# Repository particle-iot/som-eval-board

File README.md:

# M.2 SoM Evaluation Board

*Hardware repository for the M.2 SoM evaluation board*

The description of the board and its features can be found in the documentation:

[https://docs.particle.io/datasheets/cellular/b-series-eval-board/](https://docs.particle.io/datasheets/cellular/b-series-eval-board/)

In this repository you can find the following directories:

- eagle: The [Eagle CAD](https://www.autodesk.com/products/eagle/overview) design files for this board. Note that it is a 4-layer board so you won't be able to edit it with the free version.
- gerbers: The Gerber files used to manufacture the board.
- bom: The bill of materials (Excel spreadsheet).

Other useful resources include:

- [Creating your first SoM board tutorial](https://docs.particle.io/tutorials/hardware-projects/som-first-board/).
- [AN001 Basic SoM Design](https://github.com/particle-iot/app-notes/tree/master/AN001-Basic-SoM-Design) is a simple SoM base board. Like a Boron it can be powered by LiPo battery, USB, or an external DC supply. It includes: RGB LED, bq24195 PMIC, MAX17043 Fuel Gauge, USB Connector, LiPo Connector (JST-PH), and M.2 SoM Connector. It is a 2-layer board.

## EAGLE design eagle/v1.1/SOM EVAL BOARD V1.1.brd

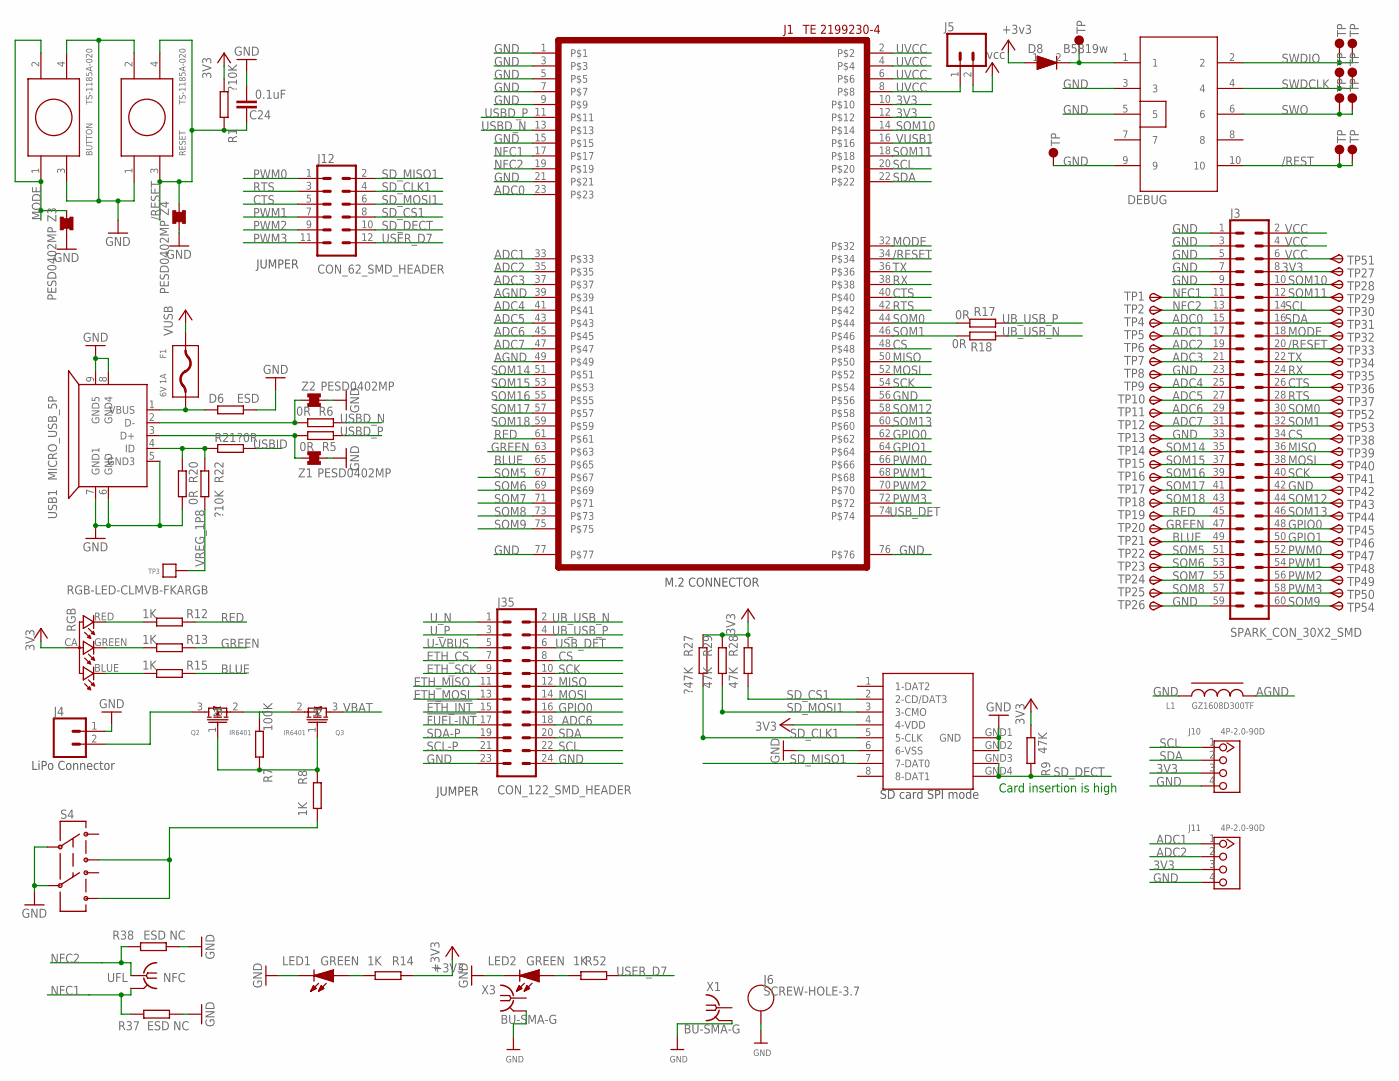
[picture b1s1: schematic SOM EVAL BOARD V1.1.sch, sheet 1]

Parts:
BUTTON: TS-1185A-020
C24: 0.1uF; C0402_B
D6: ESD; R-0402S
D8: B5819w; SOD-123
DEBUG: CON5X2; CON5X2_1.27
F1: 6V 1A; F0805
J1: TE 2199230-4; M.2EKEY
J3: SPARK_CON_30X2_SMD
J4: CONN_02-JST-2MM-SMT; JST-2-SMD
J5: CONN_02; 1X02
J6: SCREW-HOLE-3.7
J10, J11: 4P-2.0-90D; HW4-2.0-90D
J12: CON_62_SMD_HEADER; CON_6*2_SMD_HEADER
J35: CON_122_SMD_HEADER; CON_12*2_SMD_HEADER
L1: GZ1608D300TF; R-0603A
LED1, LED2: GREEN; LED0603
NFC: UFL; IPEX-20279-001E
P1, P2, P3, P4: SPARK_POGOPIN; SPARK_POGO-2.0
Q2, Q3: IR6401; SOT-23
R1, R22: ?10K; R-0402S
R5, R6, R17, R18, R20: 0R; R-0402S
R7: 100K; R0603
R8, R12, R13, R14, R15, R52: 1K; R-0402S
R9, R28, R29: 47K; R-0402S
R21: ?0R; R-0402S
R27: ?47K; R-0402S
R37, R38: ESD NC; R-0402S
RESET: TS-1185A-020
RGB: RGB-LED-CLMVB-FKARGB; PLCC4-2MM-RGB
S4: SWITCH-DPDT; SWITCH-2.5X3.2-6
TP1, TP2, TP4, TP5, TP6, TP7, TP8, TP9, TP10, TP11, TP12, TP13, TP14, TP15, TP16, TP17, TP18, TP19, TP20, TP21, TP22, TP23, TP24, TP25, TP26, TP27, TP28, TP29, TP30, TP31, TP32, TP33, TP34, TP35, TP36, TP37, TP38, TP39, TP40, TP41, TP42, TP43, TP44, TP45, TP46, TP47, TP48, TP49, TP50, TP51, TP52, TP53, TP54: TPSB1,27; B1,27
TP3: TPTP; TP
U$1, U$2, U$9, U$10, U$11, U$12: TP2; TP70_BOT
USB1: MICRO_USB_5P; MICRO_USB
X1, X3: BU-SMA-G
X4: 0046_15TW-882; SDCARD-15TW-8821
Z1, Z2, Z3, Z4: PESD0402MP; SMD-0402MP

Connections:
3V3: J1.10, J1.12, J3.8, J10.3, J11.3, R1.2, R9.2, R27.1, R28.1, R29.1, RGB.CA (1), TP27.TP, X4.4 (4-VDD); also elsewhere on the board
!ETH_INT: J35.15; also elsewhere on the board
!FUEL-INT: J35.17; also elsewhere on the board
+3V3: D8.1, R14.1; also elsewhere on the board
/RESET: C24.2, J1.34, J3.20, R1.1, RESET.3, RESET.4, TP33.TP, Z4.2
/REST: DEBUG.10, P4.P$2, U$12.P$1
ADC0: J1.23, J3.15, TP4.TP
ADC1: J1.33, J3.17, J11.1, TP5.TP
ADC2: J1.35, J3.19, J11.2, TP6.TP
ADC3: J1.37, J3.21, TP7.TP
ADC4: J1.41, J3.25, TP9.TP
ADC5: J1.43, J3.27, TP10.TP
ADC6: J1.45, J3.29, J35.18, TP11.TP
ADC7: J1.47, J3.31, TP12.TP; also elsewhere on the board
AGND: J1.39, J1.49, L1.2
BLUE: J1.65, J3.49, R15.1, TP21.TP
CS: J1.48, J3.34, J35.8, TP38.TP
CTS: J1.40, J3.26, J12.5, TP36.TP
D+: R5.2, USB1.3 (D+), Z1.2
D-: R6.2, USB1.2 (D-), Z2.2
ETH_CS: J35.7; also elsewhere on the board
ETH_MISO: J35.11; also elsewhere on the board
ETH_MOSI: J35.13; also elsewhere on the board
ETH_SCK: J35.9; also elsewhere on the board
GND: BUTTON.3, BUTTON.4, C24.1, D6.1, DEBUG.3, DEBUG.5, DEBUG.9, J1.1, J1.3, J1.5, J1.7, J1.9, J1.15, J1.21, J1.56, J1.76, J1.77, J3.1, J3.3, J3.5, J3.7, J3.9, J3.23, J3.33, J3.42, J3.59, J4.1 (2), J6.P$1, J10.4, J11.4, J35.23, J35.24, L1.1, LED1.2 (K), LED2.2 (K), R20.2, R37.2, R38.1, RESET.1, RESET.2, S4.2, S4.5, TP8.TP, TP13.TP, TP26.TP, TP42.TP, U$2.P$1, USB1.5 (GND3), USB1.6 (GND), USB1.7 (GND1), USB1.8 (GND4), USB1.9 (GND5), X1.2, X1.3 (2), X1.4 (2), X1.5 (2), X3.2, X3.3 (2), X3.4 (2), X3.5 (2), X4.6 (6-VSS), X4.GND1 (GND), X4.GND2 (GND1), Z1.1, Z2.1, Z3.1, Z4.1; also elsewhere on the board
GPIO0: J1.62, J3.48, J35.16, TP45.TP
GPIO1: J1.64, J3.50, TP46.TP
GREEN: J1.63, J3.47, R13.1, TP20.TP
MISO: J1.50, J3.36, J35.12, TP39.TP
MODE: BUTTON.1, BUTTON.2, J1.32, J3.18, TP32.TP, Z3.2
MOSI: J1.52, J3.38, J35.14, TP40.TP
unnamed: R20.1, R21.1, R22.1, USB1.4 (ID)
unnamed: R12.2, RGB.RED (4)
unnamed: R8.2, S4.3, S4.6
unnamed: D8.2, DEBUG.1, U$1.P$1
unnamed: J4.2 (1), Q2.3
unnamed: D6.2, F1.P$1 (1), USB1.1 (VBUS)
unnamed: LED1.1 (A), R14.2
unnamed: R15.2, RGB.BLUE (2)
unnamed: R13.2, RGB.GREEN (3)
unnamed: LED2.1 (A), R52.2
unnamed: Q2.2, Q3.2, R7.2
unnamed: Q2.1, Q3.1, R7.1, R8.1
NFC1: J1.17, J3.11, NFC.2@1 (GND), NFC.2@2 (GND), R37.1, TP1.TP
NFC2: J1.19, J3.13, NFC.1, R38.2, TP2.TP
PWM0: J1.66, J3.52, J12.1, TP47.TP
PWM1: J1.68, J3.54, J12.7, TP48.TP
PWM2: J1.70, J3.56, J12.9, TP49.TP
PWM3: J1.72, J3.58, J12.11, TP50.TP
RED: J1.61, J3.45, R12.1, TP19.TP
RTS: J1.42, J3.28, J12.3, TP37.TP
RX: J1.38, J3.24, TP35.TP
SCK: J1.54, J3.40, J35.10, TP41.TP
SCL: J1.20, J3.14, J10.1, J35.22, TP30.TP
SCL-P: J35.21; also elsewhere on the board
SDA: J1.22, J3.16, J10.2, J35.20, TP31.TP
SDA-P: J35.19; also elsewhere on the board
SD_CLK1: J12.4, R27.2, X4.5 (5-CLK)
SD_CS1: J12.8, R28.2, X4.2 (2-CD/DAT3)
SD_DECT: J12.10, R9.1, X4.GND3 (GND2), X4.GND4 (GND3)
SD_MISO1: J12.2, X4.7 (7-DAT0)
SD_MOSI1: J12.6, R29.2, X4.3 (3-CMO)
SOM0: J1.44, J3.30, R17.2, TP52.TP
SOM1: J1.46, J3.32, R18.2, TP53.TP
SOM5: J1.67, J3.51, TP22.TP
SOM6: J1.69, J3.53, TP23.TP
SOM7: J1.71, J3.55, TP24.TP
SOM8: J1.73, J3.57, TP25.TP
SOM9: J1.75, J3.60, TP54.TP
SOM10: J1.14, J3.10, TP28.TP
SOM11: J1.18, J3.12, TP29.TP
SOM12: J1.58, J3.44, TP43.TP
SOM13: J1.60, J3.46, TP44.TP
SOM14: J1.51, J3.35, TP14.TP
SOM15: J1.53, J3.37, TP15.TP
SOM16: J1.55, J3.39, TP16.TP
SOM17: J1.57, J3.41, TP17.TP
SOM18: J1.59, J3.43, TP18.TP
SWDCLK: DEBUG.4, P2.P$2, U$10.P$1
SWDIO: DEBUG.2, P1.P$2, U$9.P$1
SWO: DEBUG.6, P3.P$2, U$11.P$1
TX: J1.36, J3.22, TP34.TP
U-VBUS: J35.5; also elsewhere on the board
UB_USB_N: J35.2, R18.1
UB_USB_P: J35.4, R17.1
USBD_N: J1.13, R6.1; also elsewhere on the board
USBD_P: J1.11, R5.1; also elsewhere on the board
USBID: R21.2
USB_DET: J1.74, J35.6
USER_D7: J12.12, R52.1
UVCC: J1.2, J1.4, J1.6, J1.8, J5.1
U_N: J35.1; also elsewhere on the board
U_P: J35.3; also elsewhere on the board
VBAT: Q3.3; also elsewhere on the board
VCC: J3.2, J3.4, J3.6, J5.2, TP51.TP; also elsewhere on the board
VREG_1P8: R22.2, TP3.P$1
VUSB: F1.P$2 (2); also elsewhere on the board
VUSB1: J1.16; also elsewhere on the board

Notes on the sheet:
SD card SPI mode
LiPo Connector
JUMPER
Card insertion is high
M.2 CONNECTOR

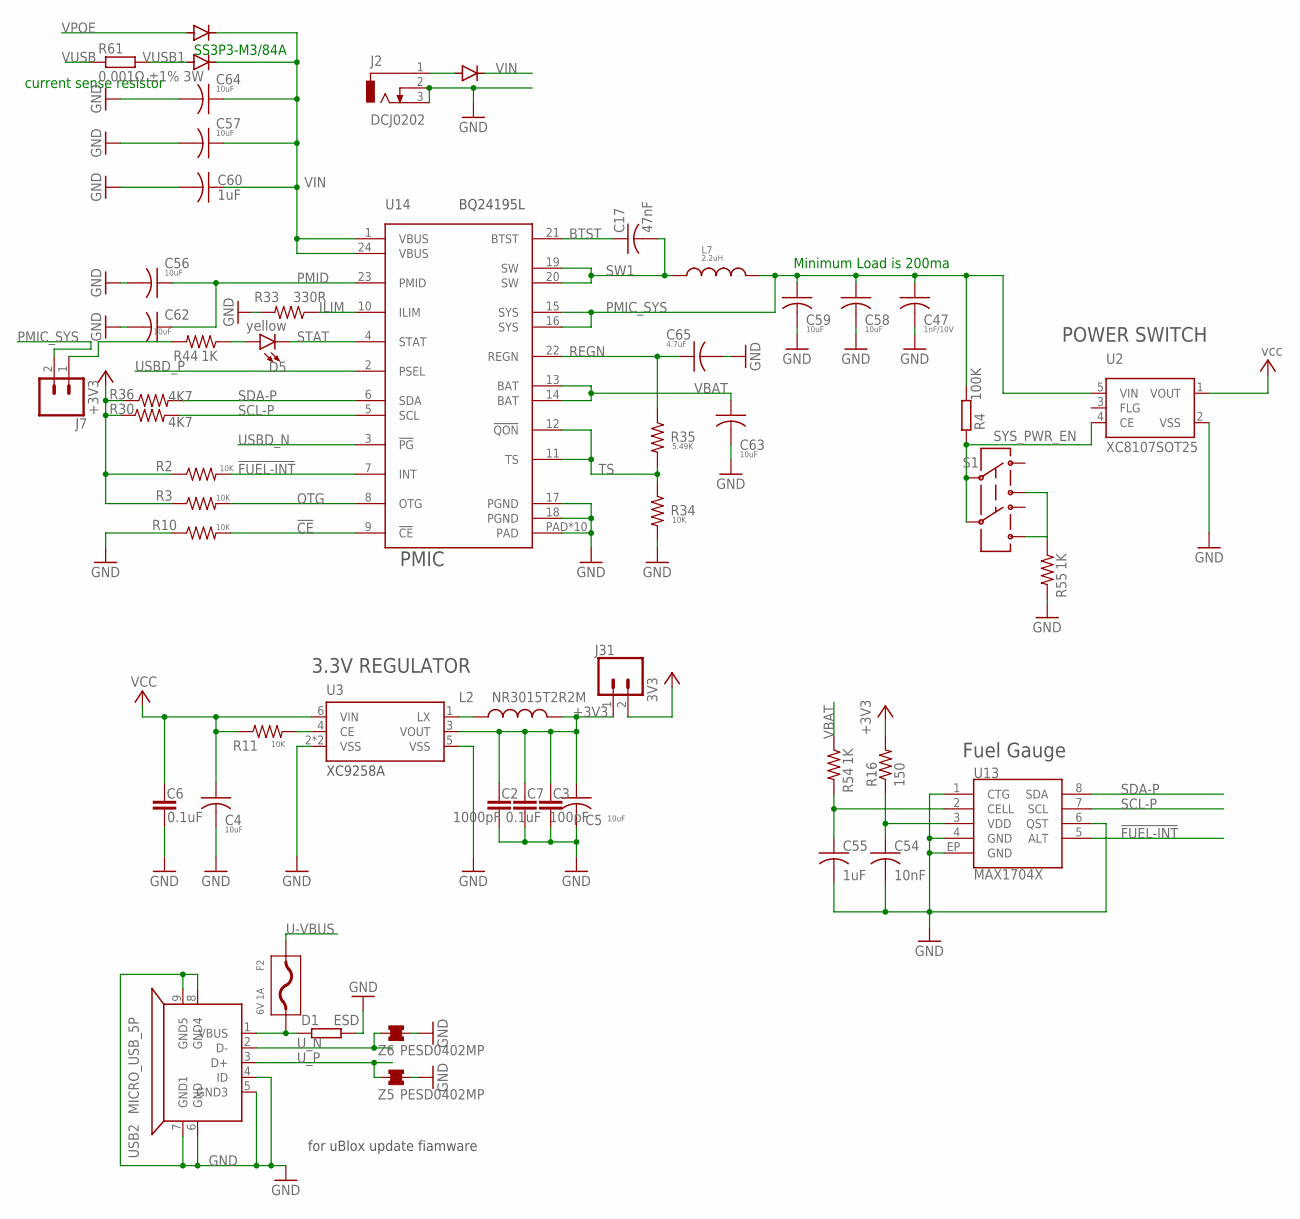
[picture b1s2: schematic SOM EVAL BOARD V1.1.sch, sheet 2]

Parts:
C2: 1000pF; C0402_B
C3: 100pF; C0402_B
C4, C5, C56, C57, C58, C59, C62, C63, C64: 10uF; C0603_B
C6, C7: 0.1uF; C0402_B
C17: 47nF; C0201_B
C47: 1nF/10V; C0402_B
C54: 10nF; C0402_B
C55, C60: 1uF; C0402_B
C65: 4.7uF; C0603_B
D1: ESD; R-0402S
D3, D4, D7: SS3P3-M3/84A; DIODE-DO-220AA_NT(SMP)
D5: yellow; LED-0603
F2: 6V 1A; F0805
J2: DCJ0202
J7, J31: CONN_02; 1X02
L2: NR3015T2R2M; INDUCTOR-VLS-E
L7: 2.2uH; INDUCTOR-4040
R2, R3, R10, R11, R34: 10K; R0402_B
R4: 100K; R0603
R16: 150; 0402-RES
R30, R36: 4K7; C0201_B
R33: 330R; R0402_B
R35: 5.49K; R0402_B
R44, R54, R55: 1K; R0402_B
R61: 0.001Ω ±1% 3W; R2512
S1: SWITCH-DPDT; SWITCH-2.5X3.2-6
U2: XC8107SOT25; SOT25
U3: XC9258A; USP-6C
U13: MAX1704X; TDFN-8
U14: BQ24195L; QFN24
USB2: MICRO_USB_5P; MICRO_USB
Z5, Z6: PESD0402MP; SMD-0402MP

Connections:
3V3: J31.2; also elsewhere on the board
!CE: R10.2, U14.9 (!CE)
!FUEL-INT: R2.2, U13.5 (ALT), U14.7 (INT); also elsewhere on the board
+3V3: C2.2, C3.2, C5.1, C7.2, J31.1, L2.P$2 (2), R2.1, R3.1, R16.2, R30.1, R36.1, U3.3 (VOUT); also elsewhere on the board
BTST: C17.1, U14.21 (BTST)
GND: C2.1, C3.1, C4.2, C5.2, C6.1, C7.1, C47.2, C54.2, C55.2, C56.2, C57.2, C58.2, C59.2, C60.2, C62.2, C63.2, C64.2, C65.2, D1.1, J2.2, J2.3, R10.1, R33.2, R34.2, R55.2, U2.2 (VSS), U3.2 (VSS), U3.5 (VSS), U3.P$1 (VSS), U13.1 (CTG), U13.4 (GND), U13.6 (QST), U13.EP (GND), U14.17 (PGND), U14.18 (PGND), U14.PAD, U14.PAD@1 (PAD), U14.PAD@2 (PAD), U14.PAD@3 (PAD), U14.PAD@4 (PAD), U14.PAD@5 (PAD), U14.PAD@6 (PAD), U14.PAD@7 (PAD), U14.PAD@8 (PAD), U14.PAD@9 (PAD), USB2.4 (ID), USB2.5 (GND3), USB2.6 (GND), USB2.7 (GND1), USB2.8 (GND4), USB2.9 (GND5), Z5.1, Z6.1; also elsewhere on the board
ILIM: R33.1, U14.10 (ILIM)
unnamed: D5.A, R44.1
unnamed: J7.1, R44.2
unnamed: D1.2, F2.P$1 (1), USB2.1 (VBUS)
unnamed: L2.P$1 (1), U3.1 (LX)
unnamed: R11.2, U3.4 (CE)
unnamed: R55.1, S1.3, S1.6
unnamed: D7.ANODE, J2.1
unnamed: C54.1, R16.1, U13.3 (VDD)
unnamed: C55.1, R54.2, U13.2 (CELL)
OTG: R3.2, U14.8 (OTG)
PMIC_SYS: C47.1, C58.1, C59.1, J7.2, L7.P$2 (2), R4.2, U2.5 (VIN), U14.15 (SYS), U14.16 (SYS)
PMID: C56.1, C62.1, U14.23 (PMID)
REGN: C65.1, R35.1, U14.22 (REGN)
SCL-P: R30.2, U13.7 (SCL), U14.5 (SCL); also elsewhere on the board
SDA-P: R36.2, U13.8 (SDA), U14.6 (SDA); also elsewhere on the board
STAT: D5.C, U14.4 (STAT)
SW1: C17.2, L7.P$1 (1), U14.19 (SW), U14.20 (SW)
SYS_PWR_EN: R4.1, S1.2, S1.5, U2.4 (CE)
TS: R34.1, R35.2, U14.11 (TS), U14.12 (!QON)
U-VBUS: F2.P$2 (2); also elsewhere on the board
USBD_N: U14.3 (!PG); also elsewhere on the board
USBD_P: U14.2 (PSEL); also elsewhere on the board
U_N: USB2.2 (D-), Z6.2; also elsewhere on the board
U_P: USB2.3 (D+), Z5.2; also elsewhere on the board
VBAT: C63.1, R54.1, U14.13 (BAT), U14.14 (BAT); also elsewhere on the board
VCC: C4.1, C6.2, R11.1, U2.1 (VOUT), U3.6 (VIN); also elsewhere on the board
VIN: C57.1, C60.1, C64.1, D3.CATHODE, D4.CATHODE, D7.CATHODE, U14.1 (VBUS), U14.24 (VBUS)
VPOE: D3.ANODE; also elsewhere on the board
VUSB: R61.1; also elsewhere on the board
VUSB1: D4.ANODE, R61.2; also elsewhere on the board

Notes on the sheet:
POWER SWITCH
3.3V REGULATOR
for uBlox update fiamware
SS3P3-M3/84A
current sense resistor
Fuel Gauge
Minimum Load is 200ma
PMIC

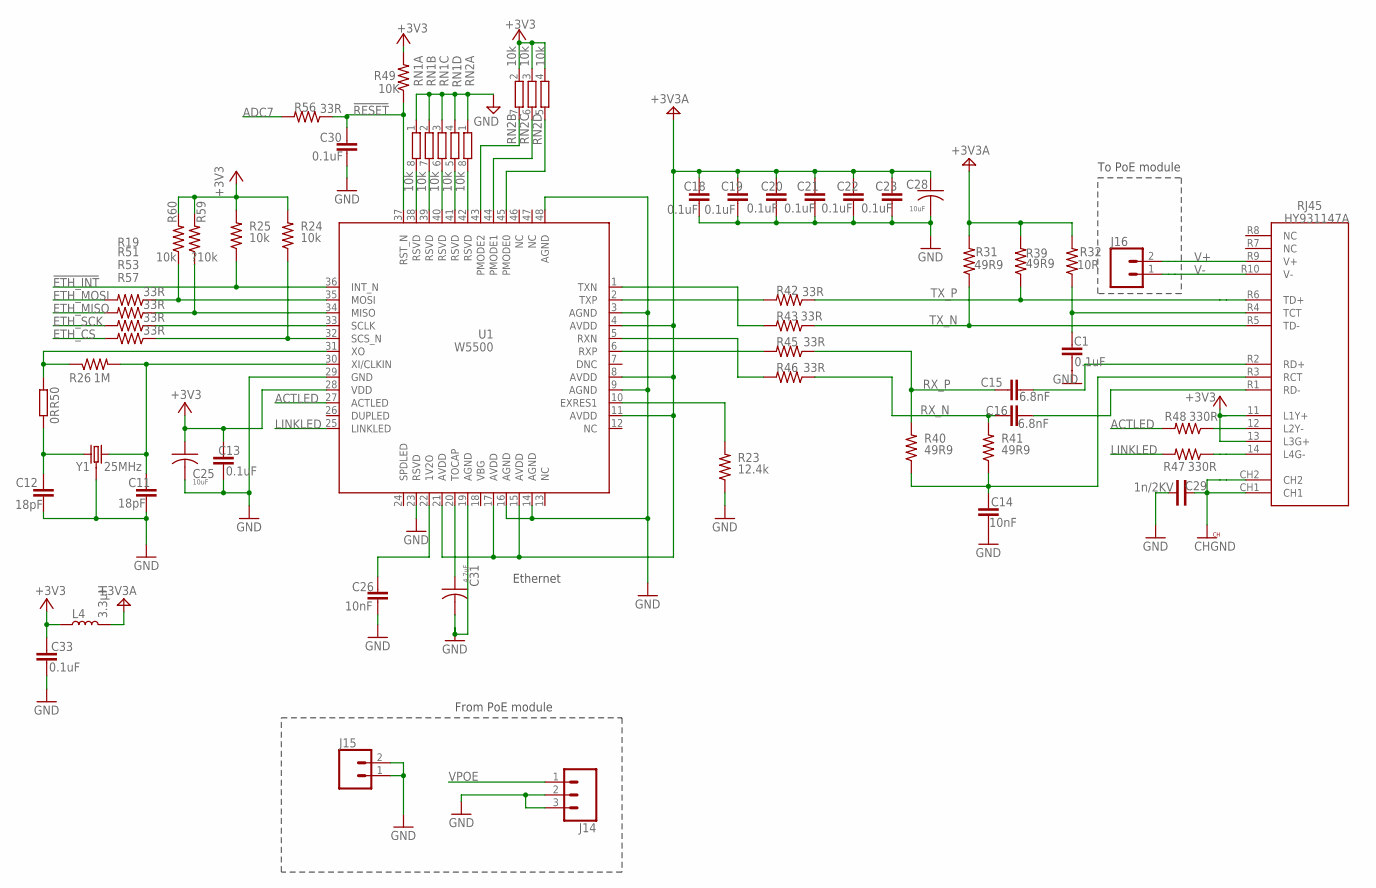
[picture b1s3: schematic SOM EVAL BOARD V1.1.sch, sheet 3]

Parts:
C1, C13, C18, C19, C20, C21, C22, C23, C30, C33: 0.1uF; C0402_B
C11, C12: 18pF; C0402_B
C14, C26: 10nF; C0402_B
C15, C16: 6.8nF; C0402_B
C25, C28: 10uF; C0603_B
C29: 1n/2KV; C-1808
C31: 4.7uF; C0603_B
J14: CONN_03; 1X03
J15, J16: CONN_02; 1X02
L4: 3.3µH; 0805
R19, R42, R43, R45, R46, R51, R53, R56, R57: 33R; R0402_B
R23: 12.4k; R0402_B
R24, R25, R60: 10k; R0402_B
R26: 1M; R0402_B
R31, R39, R40, R41: 49R9; R0402_B
R32: 10R; R0402_B
R47, R48: 330R; R0402_B
R49: 10K; R0402_B
R50: 0R; R-0402S
R59: ?10k; R0402_B
RJ45: HY931147A; ARDUINO-ETHERNET-SHIELD2-V2_CONNETTORI_POE-RJ45
RN1, RN2: 10k; 4X0402ARV341
U1: W5500
Y1: 25MHz; CRYSTAL-SMD-3.2X2.5MM

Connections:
!ETH_INT: R25.1, U1.36 (INT_N); also elsewhere on the board
!RESET: C30.2, R49.1, R56.1, U1.37 (RST_N)
+3V3: C13.2, C25.1, C33.2, L4.1, R24.2, R25.2, R49.2, R59.2, R60.2, RJ45.11 (L1Y+), RJ45.13 (L3G+), RN2.2 (1), RN2.3 (1), RN2.4 (1), U1.28 (VDD); also elsewhere on the board
+3V3A: C18.2, C19.2, C20.2, C21.2, C22.2, C23.2, C28.1, L4.2, R31.2, R32.2, R39.2, U1.4 (AVDD), U1.8 (AVDD), U1.11 (AVDD), U1.15 (AVDD), U1.17 (AVDD), U1.21 (AVDD)
ACTLED: R48.2, U1.27 (ACTLED)
ADC7: R56.2; also elsewhere on the board
CHGND: C29.P$1, RJ45.CH1, RJ45.CH2
ETH_CS: R57.2; also elsewhere on the board
ETH_MISO: R51.2; also elsewhere on the board
ETH_MOSI: R19.2; also elsewhere on the board
ETH_SCK: R53.2; also elsewhere on the board
GND: C1.1, C11.1, C12.1, C13.1, C14.1, C18.1, C19.1, C20.1, C21.1, C22.1, C23.1, C25.2, C26.1, C28.2, C29.P$2, C30.1, C31.2, C33.1, J14.2, J14.3, J15.1, J15.2, R23.1, RN1.1, RN1.2 (1), RN1.3 (1), RN1.4 (1), RN2.1, U1.3 (AGND), U1.9 (AGND), U1.14 (AGND), U1.16 (AGND), U1.19 (AGND), U1.23 (RSVD), U1.29 (GND), U1.48 (AGND), Y1.2 (3), Y1.4 (3); also elsewhere on the board
LINKLED: R47.2, U1.25 (LINKLED)
unnamed: R19.1, R60.1, U1.35 (MOSI)
unnamed: R51.1, R59.1, U1.34 (MISO)
unnamed: RN1.8 (2), U1.38 (RSVD)
unnamed: R53.1, U1.33 (SCLK)
unnamed: RN1.7 (2), U1.39 (RSVD)
unnamed: RN1.6 (2), U1.40 (RSVD)
unnamed: RN1.5 (2), U1.41 (RSVD)
unnamed: RN2.8 (2), U1.42 (RSVD)
unnamed: R24.1, R57.1, U1.32 (SCS_N)
unnamed: RN2.7 (2), U1.43 (PMODE2)
unnamed: RN2.6 (2), U1.44 (PMODE1)
unnamed: RN2.5 (2), U1.45 (PMODE0)
unnamed: C26.2, U1.22 (1V2O)
unnamed: R23.2, U1.10 (EXRES1)
unnamed: C1.2, R32.1, RJ45.R4 (TCT)
unnamed: C14.2, R40.1, R41.1, RJ45.R3 (RCT)
unnamed: R26.1, R50.1, U1.31 (XO)
unnamed: C11.2, R26.2, U1.30 (XI/CLKIN), Y1.3 (2)
unnamed: C12.2, R50.2, Y1.1
unnamed: C31.1, U1.20 (TOCAP)
unnamed: R48.1, RJ45.12 (L2Y-)
unnamed: R47.1, RJ45.14 (L4G-)
RR_N: C16.2, RJ45.R1 (RD-)
RR_P: C15.2, RJ45.R2 (RD+)
RX_N: C16.1, R41.2, R46.1
RX_P: C15.1, R40.2, R45.1
R_N: R46.2, U1.5 (RXN)
R_P: R45.2, U1.6 (RXP)
TX_N: R31.1, R43.1, RJ45.R5 (TD-)
TX_P: R39.1, R42.1, RJ45.R6 (TD+)
T_N: R43.2, U1.1 (TXN)
T_P: R42.2, U1.2 (TXP)
V+: J16.2, RJ45.R9 (V+)
V-: J16.1, RJ45.R10 (V-)
VPOE: J14.1; also elsewhere on the board

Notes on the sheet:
From PoE module
To PoE module
Ethernet

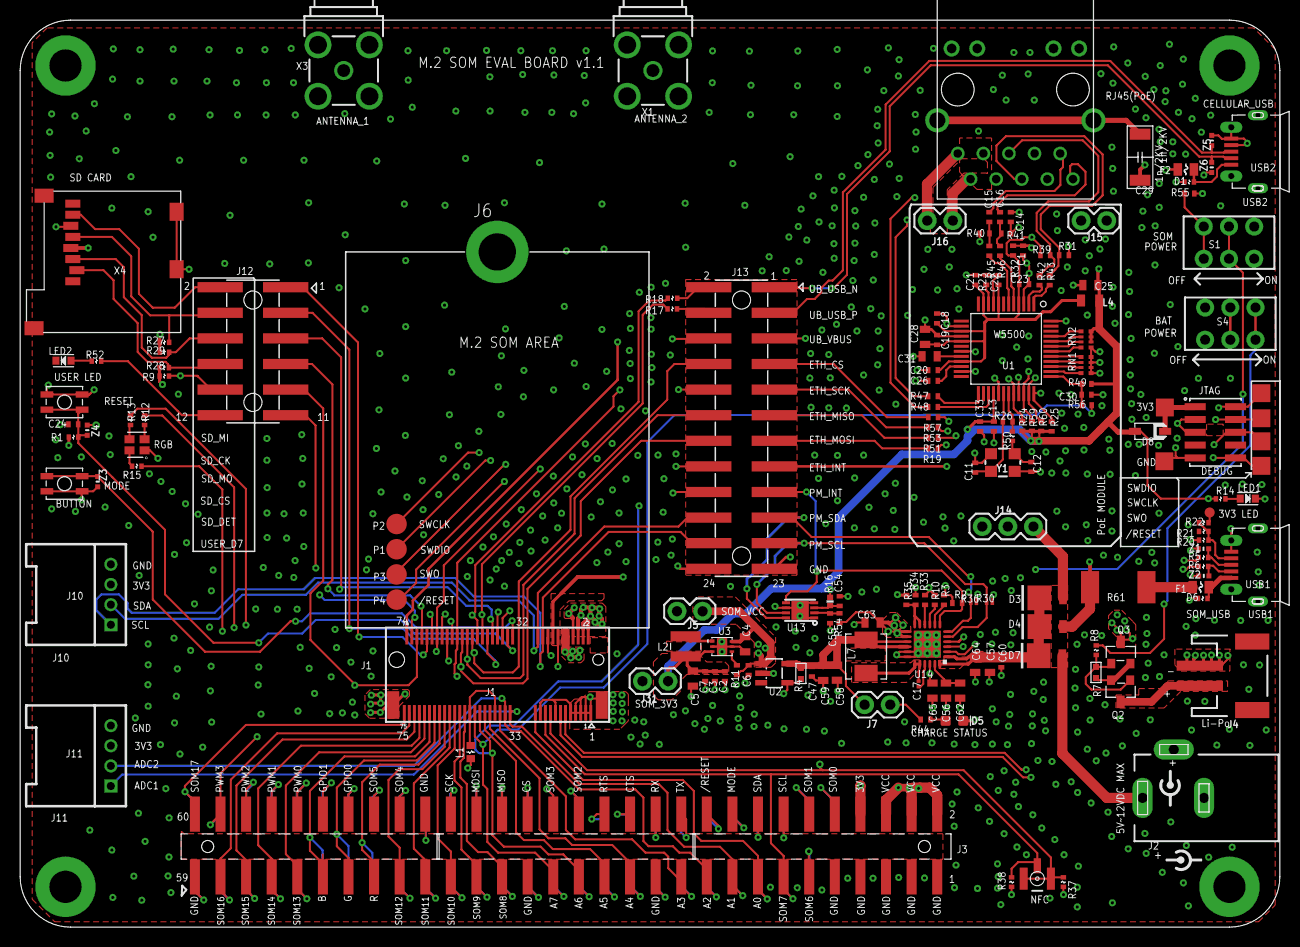
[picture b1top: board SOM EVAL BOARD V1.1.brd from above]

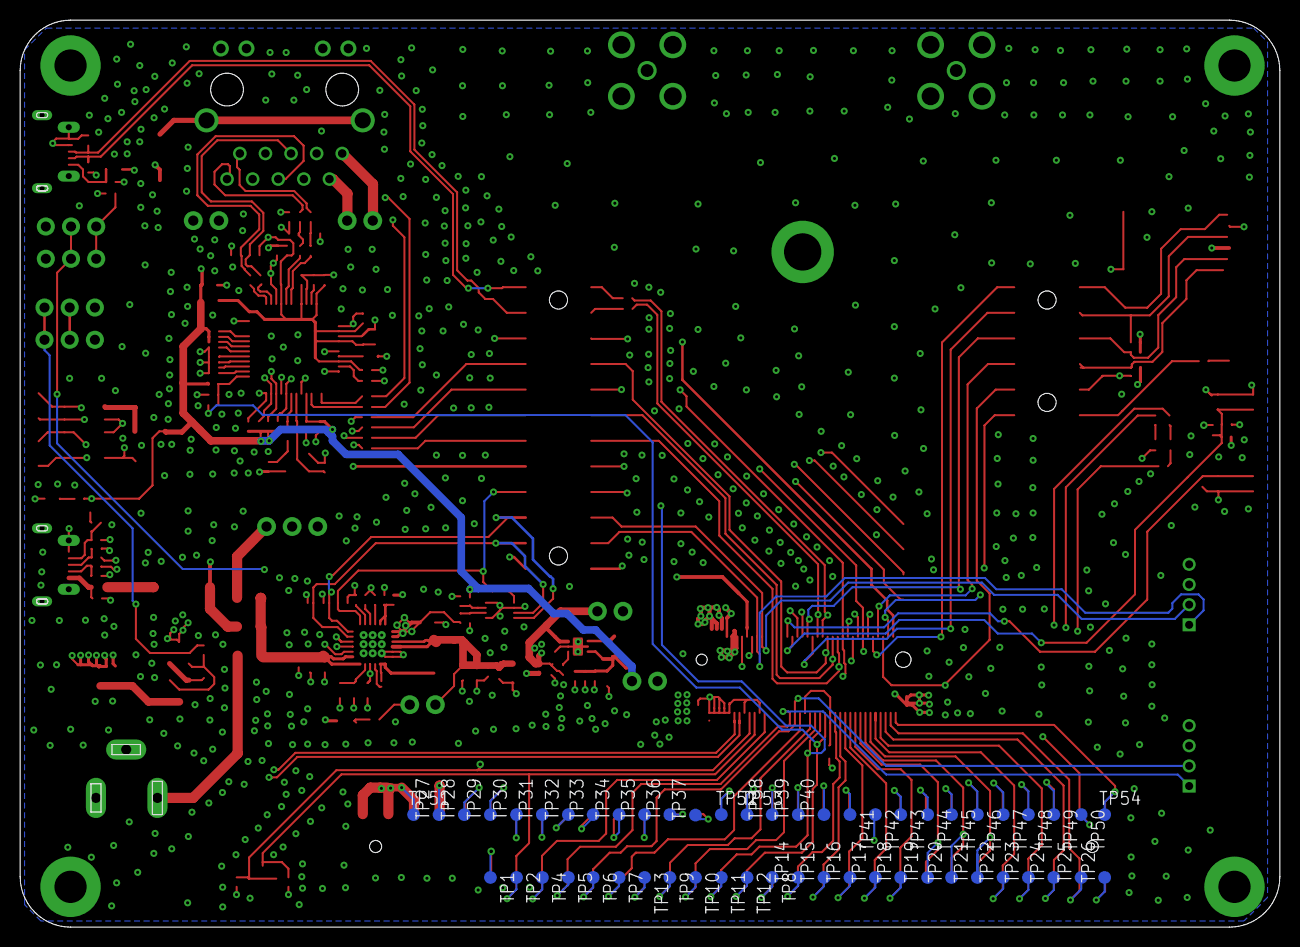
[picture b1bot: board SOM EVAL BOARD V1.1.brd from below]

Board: 4 copper layers, 125.0 x 90.0 mm, 223 parts (59 on the bottom side), 158 nets.

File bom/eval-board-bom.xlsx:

Description | Designator | Qty | MFG | MPN | MFG1 | MPN1
Ceramic Capacitor X6S 1uF 0402 6.3V ±10% ROHS | C2 | 1 | Samsung | CL05X105KQ5NNNC
CAP CER 0.1uF 16V X7R 0402 10% | C1,C6,C7,C13,C18,C19,C20,C21,C22,C23,C24,C30,C33 | 13 | Fenghua | 0402B104K160NT
CAP CER 100pF 50V X7R 0402 10% | C3 | 1 | Fenghua | 0402B101K500NT
CAP CER 10nF 16V X5R 0402 10% | C14,C26,C54 | 3 | Fenghua | 0402X105K160NT
CAP CER10uF 10V X5R 0603 10% | C4,C5,C25,C28,C58,C59,C63 | 7 | Fenghua | 0603X106K100NT
CAP CER 10UF 25V X5R 0603 20% | C56,C57,C62,C64 | 4 | Yageo | CC0603MRX5R8BB106 | Samsung | CL10A106MA8NRNC
CAP CER 18PF 50V C0G/NP0 0402 5% | C11,C12 | 2 | Samsung | CL05C180JB5NNNC
CAP CER 1000PF 2KV(3KV) X7R 1808 10% | C29 | 1 | FengHua | 1808B102K202NT | Johanson | 302R29W102KV4E
CAP CER 1000PF 50V X7R 0402 10% | C47 | 1 | SAMSUNG | CL05B102JB5NNNC
CAP CER 1UF 25V X5R 0402 10% | C55,C60 | 2 | Samsung | CL05A105KA5NQNC | FH | 0402F105M250NT
CAP CER 4.7uF 6.3V X5R 0603 10% Low ESR<70mohms | C31,C65 | 2 | Yageo | CC0603KRX5R5BB475
CAP CER 47NF 6.3V X5R 0201 10% | C17 | 1 | Murata | GRM033R60J473KE19D | FH | 0201X473K6R3NT
CAP CER 6.8nF 6.3V X7R 0402 10% | C15,C16 | 2 | muRata | GRM155R71H682KA88D
RES SMD 0 OHM JUMPER 1/16W 0402 | R5,R6,R17,R18,R20,R50, | 6 | Fenghua | RC-02000JT | YAGEO | RC0402JR-070RL
RES SMD 100K OHM 5% 1/8W 0603 | R4,R7 | 2 | Yageo | RC0603JR-07100KL
RES SMD 10K OHM 5% 1/16W 0402 | R2,R3,R10,R11,R34,R49,R24,R25,R60 | 9 | Fenghua | RC-02W103JT | YAGEO | RC0402JR-0710KL
RES SMD 10 OHM 1% 1/16W 0402 | R32 | 1 | UniOhm | 0402WGF100JTCE | YAGEO | RC0402FR-0710RL
RES ARRAY 4 RES 10K OHM 0804 1% 4RES | RN1,RN2 | 2 | YAGEO | YC124-FR-0710KL
RES SMD 0.001Ω OHM 1% 1W 2512 | R61 | 1 | YAGEO | PA2512FKF070R001E
RES SMD 12.4K OHM 1% 1/16W 0402 | R23 | 1 | YAGEO | RC0402FR-0712K4L
RES SMD 150 OHM 1% 1/16W 0402 12.4K | R16 | 1 | Yageo | RC0402FR-07150RL
RES SMD 1K OHM 5% 1/16W 0402 | R8,R12,R13,R14,R15,R52,R44,R54,R55 | 9 | Fenghua | RC-02W102JT
RES SMD 1M OHM 5% 1/16W 0402 | R26 | 1 | UniOhm | 0402WGF1004TCE | YAGEO | RC0402JR-071ML
RES SMD 330R OHM 1% 1/16W 0402 | R33,R47,R48 | 3 | Fenghua | RC-02W3300FT | YAGEO | RC0402FR-07330RL
RES SMD 33R OHM 1% 1/16W 0402 | R42,R43,R45,R46,R56,R19,R51,R53,R57 | 9 | UniOhm | 0402WGF330JTCE | YAGEO | RC0402FR-0733RL
RES SMD 47k OHM 1% 1/16W 0402 | R9,R28,R29 | 3 | YAGEO | RC0402FR-0747KL
RES SMD 49R9 OHM 1% 1/16W 0402 | R31,R39,R40,R41 | 4 | YAGEO | RC0402FR-0749R9L
RES SMD 4.7K OHM 5% 1/20W 0201 | R30,R36 | 2 | Yageo | RC0201JR-074K7L
RES SMD 5K49 OHM 1% 1/16W 0402 | R35 | 1 | Fenghua | RC-02W5491FT | Yageo | RC0402FR-075K49L
FIXED IND 2.2UH 4A 61 MOHM SMD | L7 | 1 | Bourns,Inc. | SRP4020TA-2R2M
CRYSTAL 25.0000MHZ 20PF 4-SMD 3225 20PPM | Y1 | 1 | YXC | X322525MSB4SI | EPSON | FA-238 25.0000MD-G3
FERRITE BEAD 100 OHM@100MHz 0.8A 0805 | L4 | 1 | Sunload | GZ2012D101TF
RESET FUSE 1A 6V 0805 | F1,F2 | 2 | JDTFuse | ASMD0805-100
4P-2.0-90D | J10,J11 | 2 | Kaweei | CW-A2008R-04
connector 2x5pin 1.27mm pitch SMD ROHS | DEBUG | 1 | Kaweei | P6014A-M2GC-030-10-RC
connector 2x12pin 2.54mm pitch SMD ROHS | J35 | 1 | Kaweei | P210-MFGN-058-24-PRC
connector 2x6pin 2.54mm pitch SMD ROHS | J12 | 1 | Kaweei | P210-MFGN-058-12-PRC
DC-005 outer diameter 6.4 inner core 3 feet high temperature 2.1MMDC DC power s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 | J2 | 1 | Kaweei | CDJ-D005B-2.0
female header connector 2x30pin 2.54mm pitch SMD ROHS | J3 | 1 | Kaweei | F291-MGN-D072-60-PRC
LIPO BATTERY CONNECTOR | J4 | 1 | Kaweei | CW2001-02T-M01-D
connector 2pin header，2.54mm | J5,J7,J31 | 3 | Kaweei | P101-SGP-060-030-02
connector 3pin female header，2.54mm | J14 | 1 | Kaweei | F101-SGP-D030-03
connector 2pin female header，2.54mm | J15,J16 | 2 | Kaweei | F101-SGP-D030-02
Self-elastic Internal soldering TF connector 0046_15TW-882 | X4 | 1 | Kaweei | CTFD003-S-02-BD
MSS-22D16 pin small toggle switch six feet | S1,S4 | 2
POGOPIN 2.0*3.2 | P1,P2,P3,P4 | 4 | Huarong | 2.0*3.2（需要问供应商是否可以编带）
NGFF carrier NGFF M.2 E-KEY height 4.2H SSD solid state drive slot card connect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 | J1 | 1 | LOTES | 181004 | TE | TE 2199230-4
LED blue 0603 ROHS | LED1,LED2 | 2 | Everlight | 19-217/BHC-ZM1N2TY/3T | BrtLED | BL-HB336G-TRB
FERRITE BEAD 30 OHM@100MHz 2A 0603 1LN | L1 | 1 | Sunload | GZ1608D300TF
ESD DIODE/BPESD0402-05ST | Z1,Z2,Z3,Z4,Z5,Z6 | 6 | BORN | BPESD0402-05ST
RJ45 Connector | RJ45 | 1 | HANRUN | HY931147A
P-MOS -12V 4.3A SOT23 ROHS | Q2,Q3 | 2 | IR | IRLML6401TRPBF | Force mos | ME2333
IC 2-WIRE FG MODEL GAUGE LO BATT | U13 | 1 | Maxim | MAX17043G+T
IC CHRG MGMT LI-ION/POL 24VQFN | U14 | 1 | TI | BQ24195
USB Micro Connector with Slots, SMD ROHS | USB1,USB2 | 2 | Kaweei | CMCUSB-5BFM14G-01-D
FIXED IND 2.2UH 1.5A 72 MOHM SMD | L2 | 1 | TAIYO | NRS3015T2R2MNGH | TaiyoYuden | NR3015T2R2M
LED RGB, Common Anode, Clear, 4PLCC SMD ROHS | RGB | 1 | CREE | CLMVC-FKA-CA1E1L81BB7C3C3
DIODE SCHOTTKY 30V 3A DO220AA | D3,D4,D7 | 3 | VISHAY | SS3P3-M3/84A
Tactile Switch, Black Button 2.5mm height | BUTTON,RESET | 2 | HAOYU | TS-1185A-025C
CONN UMC RCPT STR 50 OHM SMD | NFC | 1 | Kaweei | P1163-0140R
IC CTLR 3-1 ETH TCP/IP 48LQFP | U1 | 1 | wiznet | W5500
85mΩ High Function Power Switch | U2 | 1 | Torex | XC8107AC20MR-G
Synchronous Step-Down DC/DC Converters | U3 | 1 | Torex | XC9258B33CER-G
Schottky Diode B5819w SL 1A 40V ROHS | D8 | 1 | CJ江苏长电 | B5819w SL
LED super yellow 0603 ROHS | D5 | 1 | Everlight | 19-217/Y5C-AP1Q2/3T | BrtLed(佰鸿) | BL-HKC36G-AV-TRB
nut(M3,custom made) |  | 1 | Hengxintai | M3
PCB for SOM EVA 4 layers PCB 130*90mm, black matte PCB w/ cyan silkscreen |  | 1 | Benlida
Short circuit cap |  | 22 | Risym | 2.54mm black
USB Micro-B Cable |  | 1 | Hop | USB cable
Grove - Temperature & Humidity Sensor |  | 1 | Seeed | 101020011
Anti-collision rubber 8*2.5 |  | 4 | Shida | 8*2.5
screw(custom made) 3*3 |  | 2 | Hengxintai | 3*3
metal spacer M2.5*5-M |  | 2 | Hengxintai | M2.5*5-M
SMA connector with IPEX cable 40 mm | X1, X3 | 2 | Kaweei

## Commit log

2019-10-03 initial version
2019-12-18 Updated to version 1.0.1 of eval board
2020-08-27 Update license
2021-01-28 Added v1.1 board

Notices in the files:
parts and their libraries:
SparkFun-LED: Licensing: Creative Commons ShareAlike 4.0 International - https://creativecommons.org/licenses/by-sa/4.0
supressor: Copyright (C) 2009, Bob Starr
